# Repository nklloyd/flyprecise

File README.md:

# Pressure Sensor Calibration for Homemade Densimeter

The sensor outputs an analog voltage that varies with applied force. 
This voltage is converted into a digital value using `analogRead()` (range: 0–1023).

A linear calibration equation is used to convert this reading into mass

## Calibration Data

The following hardcoded values are used:

* `zeroMass = 49.8`
* `zeroReading = 778`
* `knownMass = 110.6`
* `knownReading = 259`

## Output

The program continuously:

1. Reads the analog sensor value
2. Converts it to mass using the calibration equation
3. Prints both raw reading and calculated mass to the serial monitor

```
Raw reading: 512
Mass: 85.3 g
```

---

## Known Bugs / Limitations

Different resistor values are being tested in the voltage divider to improve sensitivity and accuracy. 
Results may vary depending on the resistor.

### 2. Non-Linear Sensor Behavior

FSRs are inherently non-linear. This implementation assumes a linear relationship, which may introduce error, especially outside the calibrated range.

## Hardware Notes

* Sensor: Force-Sensitive Resistor (FSR)
* Input Pin: A0
* Microcontroller: Arduino-compatible board
* Circuit: Voltage divider (FSR + resistor)

---

## Future Work

* Implement non-linear calibration (e.g., exponential/log fit)
* Integrate mass readings into full density calculation pipeline
* Add real-time calibration interface via serial input
* Improve repeatability and measurement stability

---

## Alpha Build Documentation
* Alpha Build - https://docs.google.com/document/d/1_ZNRy5aV_9XcpFfJprM5AeEUtTBAZkFf1owPfBoO9iQ/edit?usp=sharing
* Alpha Test Plan - https://docs.google.com/document/d/1SXkQXstxGwYJmzBSkHG-z-8G0-C6oroAPGTkn4TiCtQ/edit?usp=sharing

## Beta Build Documentation
* Beta Build - https://docs.google.com/document/d/1fs_zSv_gkhbn85_mFjjC6zrKmSh5nXOdgN2fiGV2G-g/edit?usp=sharing
* Beta Test Plan - https://docs.google.com/document/d/1E2wE4QuUsBIM2U0-oblOg121ZjWiWZ_3sDpITYq9rYI/edit?tab=t.0

## Beta Presentation
* Slide Deck - https://docs.google.com/presentation/d/1BMJHcqOLjPH9VT9NJFxybecDhRv366sLr2RfTS_22i4/edit?usp=sharing

## Release Candidate Documenation
* Release Candidate - https://docs.google.com/document/d/1QZRxaM0PU--QsGB8tHn2rrG-0xElWLTbt4H6Ct_5NIU/edit?usp=sharing
* Preliminary Report - https://docs.google.com/document/d/1rlRpKkgs4_Q8DmHznruekNW2ZyRQ_ktouU92uwmhSHU/edit?usp=sharing

## Final Report 
* Final report- https://docs.google.com/document/d/1LpSjd8ndpp8v7XsZYO4TgUB53bwFvWm3DY0gWsaeNzM/edit?usp=sharing

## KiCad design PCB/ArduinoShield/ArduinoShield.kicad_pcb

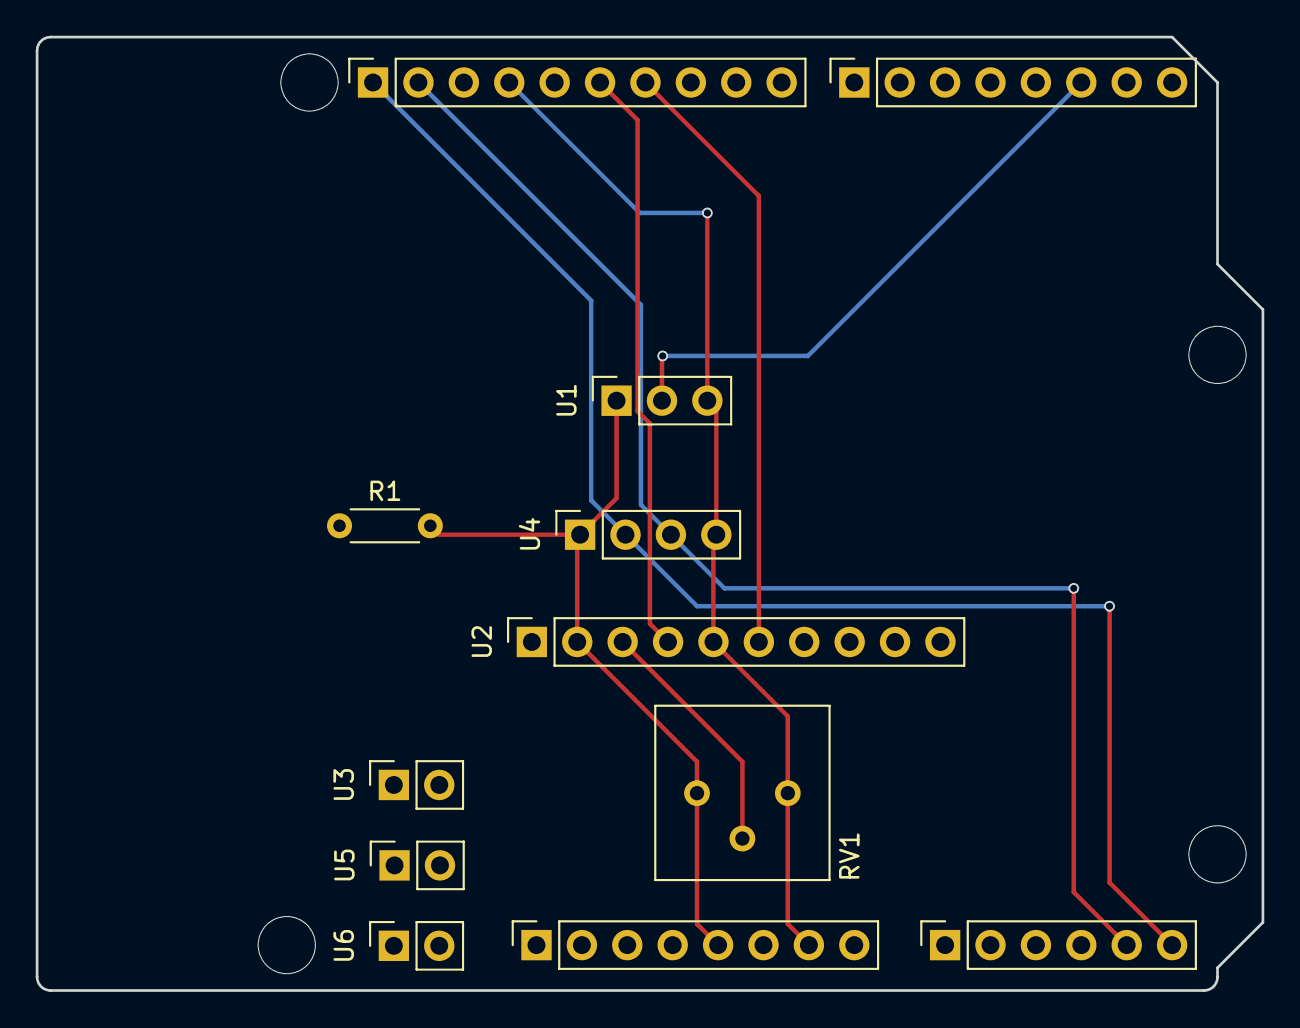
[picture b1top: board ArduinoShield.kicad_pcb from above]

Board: 2 copper layers, 68.6 x 53.3 mm, 16 parts (0 on the bottom side), 8 nets.

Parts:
J1: Power; PinSocket_1x08_P2.54mm_Vertical
J2: Digital/PWM; PinSocket_1x10_P2.54mm_Vertical
J3: Analog; PinSocket_1x06_P2.54mm_Vertical
J4: Digital/PWM; PinSocket_1x08_P2.54mm_Vertical
MH1, MH2, MH3, MH4: MountingHole_3.2mm
R1: R; R_Axial_DIN0204_L3.6mm_D1.6mm_P5.08mm_Horizontal
RV1: R_Potentiometer_Trim; Potentiometer_Bourns_3386P_Vertical
U1: PinSocket_1x03_P2.54mm_Vertical
U2: PinSocket_1x10_P2.54mm_Vertical
U3, U5, U6: PinSocket_1x02_P2.54mm_Vertical
U4: PinSocket_1x04_P2.54mm_Vertical

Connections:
+5V: J1.5, R1.2, RV1.1, U1.1 (VIN), U2.2 (VDD), U4.1 (VIN)
/2: J4.6, U1.2 (DIN)
/12: J2.6, U2.4 (RS)
/*11: J2.7, U2.6 (E)
/SCL/A5: J2.1, J3.6, U4.2 (SCL)
/SDA/A4: J2.2, J3.5, U4.3 (SDA)
GND: J1.6, J1.7, J2.4, RV1.3, U1.3 (GND), U2.1 (VSS), U2.5 (R/W), U4.4 (GND)
unnamed: RV1.2, U2.3 (V0)

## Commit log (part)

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2026-04-13 Innit
2026-04-16 Add files via upload
    File containing arduino code
2026-04-16 Changed readme
